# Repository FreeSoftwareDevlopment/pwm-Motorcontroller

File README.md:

# pwm-Motorcontroller
Control a Motor over Poti with PWM KiCad Project

- 
- 

&copy; Sharkbyteprojects

---

AD:

## Prototyping Services

- [Aisler](https://aisler.net)
- [JLCpcb](https://jlcpcb.com)

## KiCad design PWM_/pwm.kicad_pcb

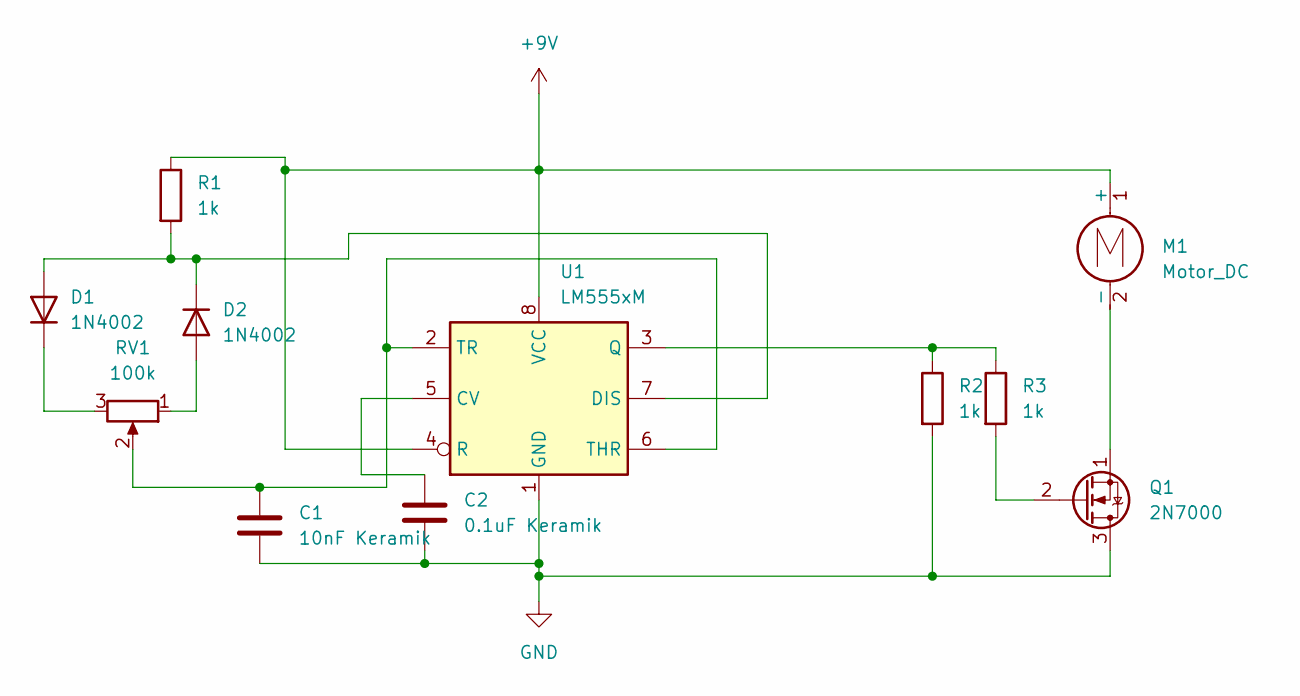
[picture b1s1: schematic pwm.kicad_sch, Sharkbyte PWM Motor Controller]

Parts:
C1: 10nF Keramik
C2: 0.1uF Keramik; C_Disc_D12.0mm_W4.4mm_P7.75mm
D1, D2: 1N4002; D_DO-41_SOD81_P10.16mm_Horizontal
M1: Motor_DC
Q1: 2N7000; TO-92_Inline
R1, R2, R3: 1k; R_Axial_DIN0309_L9.0mm_D3.2mm_P15.24mm_Horizontal
RV1: 100k
U1: LM555xM; SOIC-8_3.9x4.9mm_P1.27mm

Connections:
GND: C1.2, C2.2, Q1.3 (D), R2.2, U1.1 (GND); also elsewhere on the board
unnamed: D1.1 (K), RV1.3
unnamed: D1.2 (A), D2.1 (K), R1.2, U1.7 (DIS)
unnamed: D2.2 (A), RV1.1
unnamed 4: M1.1 (+), R1.1, U1.4 (R), U1.8 (VCC); also elsewhere on the board
unnamed: M1.2 (-), Q1.1 (S)
unnamed: Q1.2 (G), R3.2
unnamed: R2.1, R3.1, U1.3 (Q)
unnamed: C2.1, U1.5 (CV)
unnamed: C1.1, RV1.2, U1.2 (TR), U1.6 (THR)

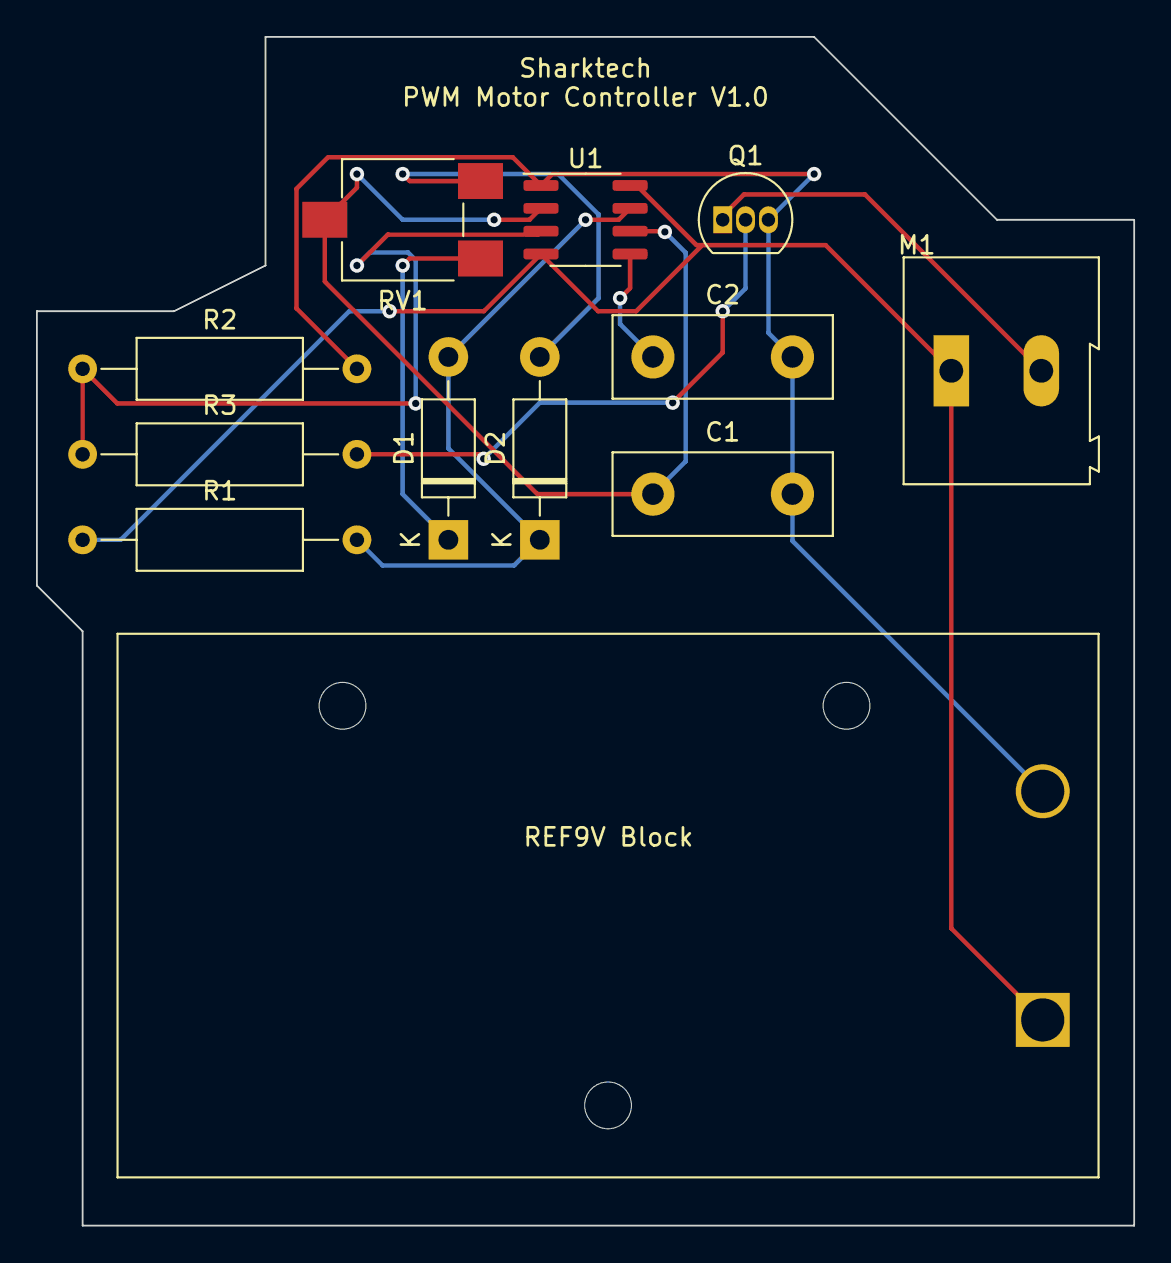
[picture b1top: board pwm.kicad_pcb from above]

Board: 2 copper layers, 61.0 x 66.0 mm, 12 parts (0 on the bottom side), 10 nets.

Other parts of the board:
REF9V Block: BatteryHolder_Eagle_12BH611-GR

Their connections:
GND: REF9V Block.2; also elsewhere on the board
unnamed 4: REF9V Block.1; also elsewhere on the board
